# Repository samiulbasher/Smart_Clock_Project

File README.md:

# Smart_Clock_Project
Smart ESP8266 based real time clock

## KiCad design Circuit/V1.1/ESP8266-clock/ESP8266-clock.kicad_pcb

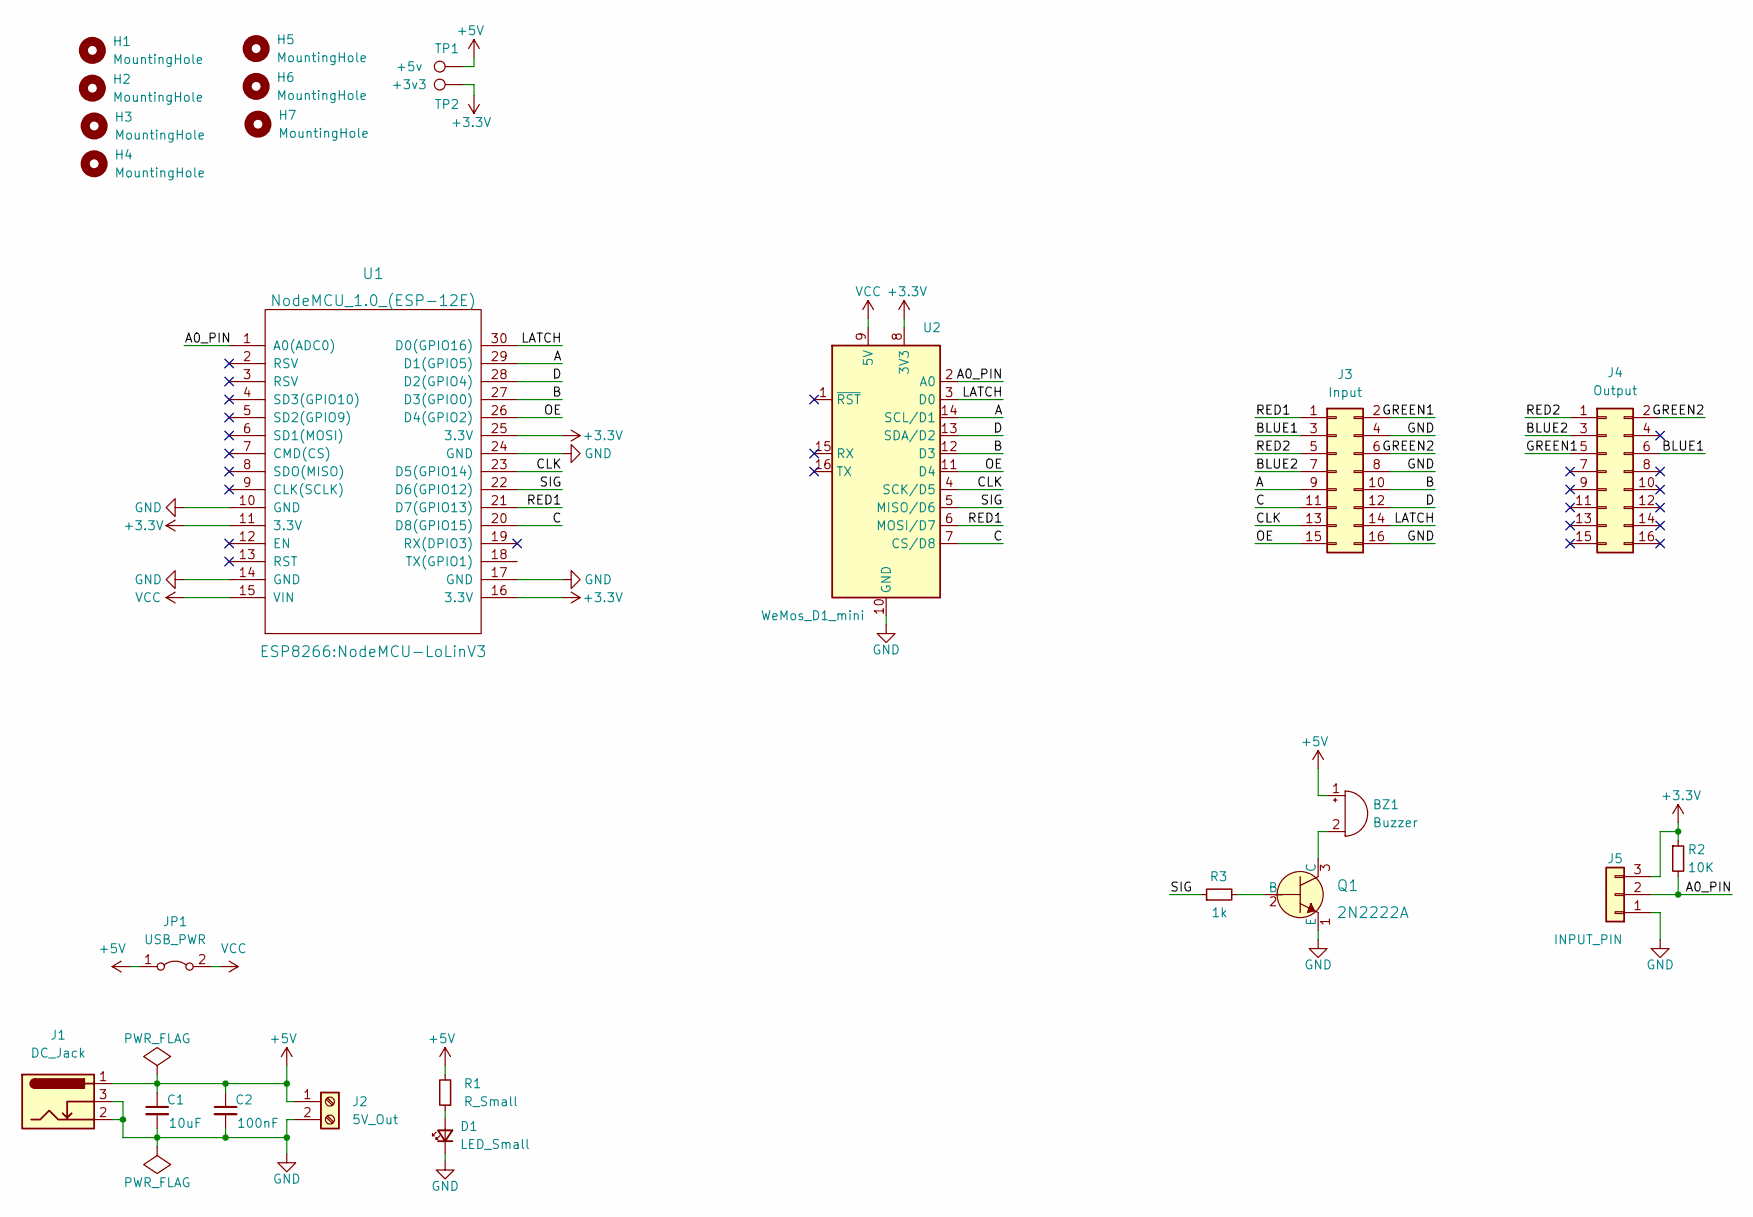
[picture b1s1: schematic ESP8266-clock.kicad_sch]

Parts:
BZ1: Buzzer; Buzzer_12x9.5RM7.6
C1: 10uF; CP_Radial_D5.0mm_P2.50mm
C2: 100nF; C_Disc_D3.0mm_W2.0mm_P2.50mm
D1: LED_Small; LED_D3.0mm
H1, H2, H3, H4: MountingHole; MountingHole_2.5mm
H5, H6, H7: MountingHole; MountingHole_3.5mm_Pad_Via
J1: DC_Jack; BarrelJack_Horizontal
J2: 5V_Out; TerminalBlock_Phoenix_PT-1,5-2-5.0-H_1x02_P5.00mm_Horizontal
J3: Input; PinHeader_2x08_P2.54mm_Vertical
J4: Output; PinHeader_2x08_P2.54mm_Vertical
J5: INPUT_PIN; Molex_KK-254_AE-6410-03A_1x03_P2.54mm_Vertical
JP1: USB_PWR; PinHeader_1x02_P2.54mm_Vertical
Q1: 2N2222A; TO-92-3_Formed_Leads; MPN 2N2222A; Digi-Key_PN 2N2222ACS-ND
R1: R_Small; R_Axial_DIN0204_L3.6mm_D1.6mm_P2.54mm_Vertical
R2: 10K; R_Axial_DIN0204_L3.6mm_D1.6mm_P7.62mm_Horizontal
R3: 1k; R_Axial_DIN0204_L3.6mm_D1.6mm_P2.54mm_Vertical
TP1: +5v; TestPoint_Pad_D1.0mm
TP2: +3v3; TestPoint_Pad_D1.0mm
U1: NodeMCU_1.0_(ESP-12E); NodeMCU-LoLinV3
U2: WeMos_D1_mini; WEMOS_D1_mini_light

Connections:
+3V3: J5.3, R2.1, TP2.1, U1.11 (3.3V), U1.16 (3.3V), U1.25 (3.3V), U2.8 (3V3)
+5V: BZ1.1 (-), C1.1, C2.1, J1.1, J2.1, JP1.1 (A), R1.2, TP1.1
/A: J3.9, U1.29 (D1(GPIO5)), U2.14 (SCL/D1)
/A0_PIN: J5.2, R2.2, U1.1 (A0(ADC0)), U2.2 (A0)
/B: J3.10, U1.27 (D3(GPIO0)), U2.12 (D3)
/BLUE1: J3.3, J4.6
/BLUE2: J3.7, J4.3
/C: J3.11, U1.20 (D8(GPIO15)), U2.7 (CS/D8)
/CLK: J3.13, U1.23 (D5(GPIO14)), U2.4 (SCK/D5)
/D: J3.12, U1.28 (D2(GPIO4)), U2.13 (SDA/D2)
/GREEN1: J3.2, J4.5
/GREEN2: J3.6, J4.2
/LATCH: J3.14, U1.30 (D0(GPIO16)), U2.3 (D0)
/OE: J3.15, U1.26 (D4(GPIO2)), U2.11 (D4)
/RED1: J3.1, U1.21 (D7(GPIO13)), U2.6 (MOSI/D7)
/RED2: J3.5, J4.1
/SIG: R3.1, U1.22 (D6(GPIO12)), U2.5 (MISO/D6)
GND: C1.2, C2.2, D1.1 (K), J1.2, J1.3, J2.2, J3.4, J3.8, J3.16, J5.1, Q1.1 (E), U1.10 (GND), U1.14 (GND), U1.17 (GND), U1.24 (GND), U2.10 (GND)
unnamed: BZ1.2 (+), Q1.3 (C)
unnamed: D1.2 (A), R1.1
unnamed: Q1.2 (B), R3.2
VCC: JP1.2 (B), U1.15 (VIN), U2.9 (5V)

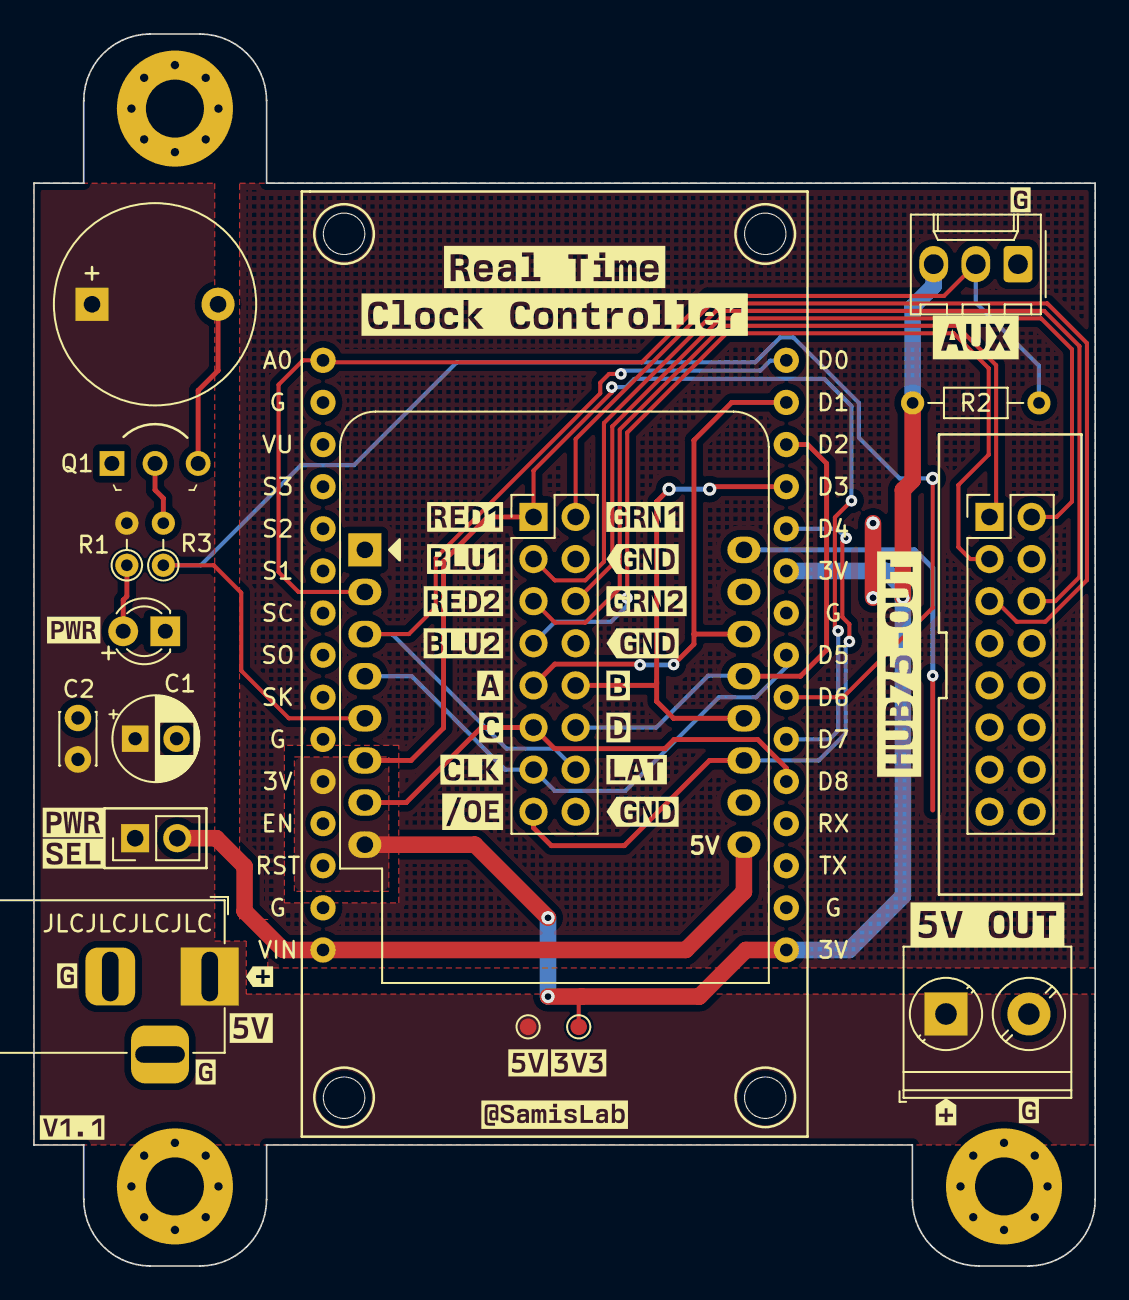
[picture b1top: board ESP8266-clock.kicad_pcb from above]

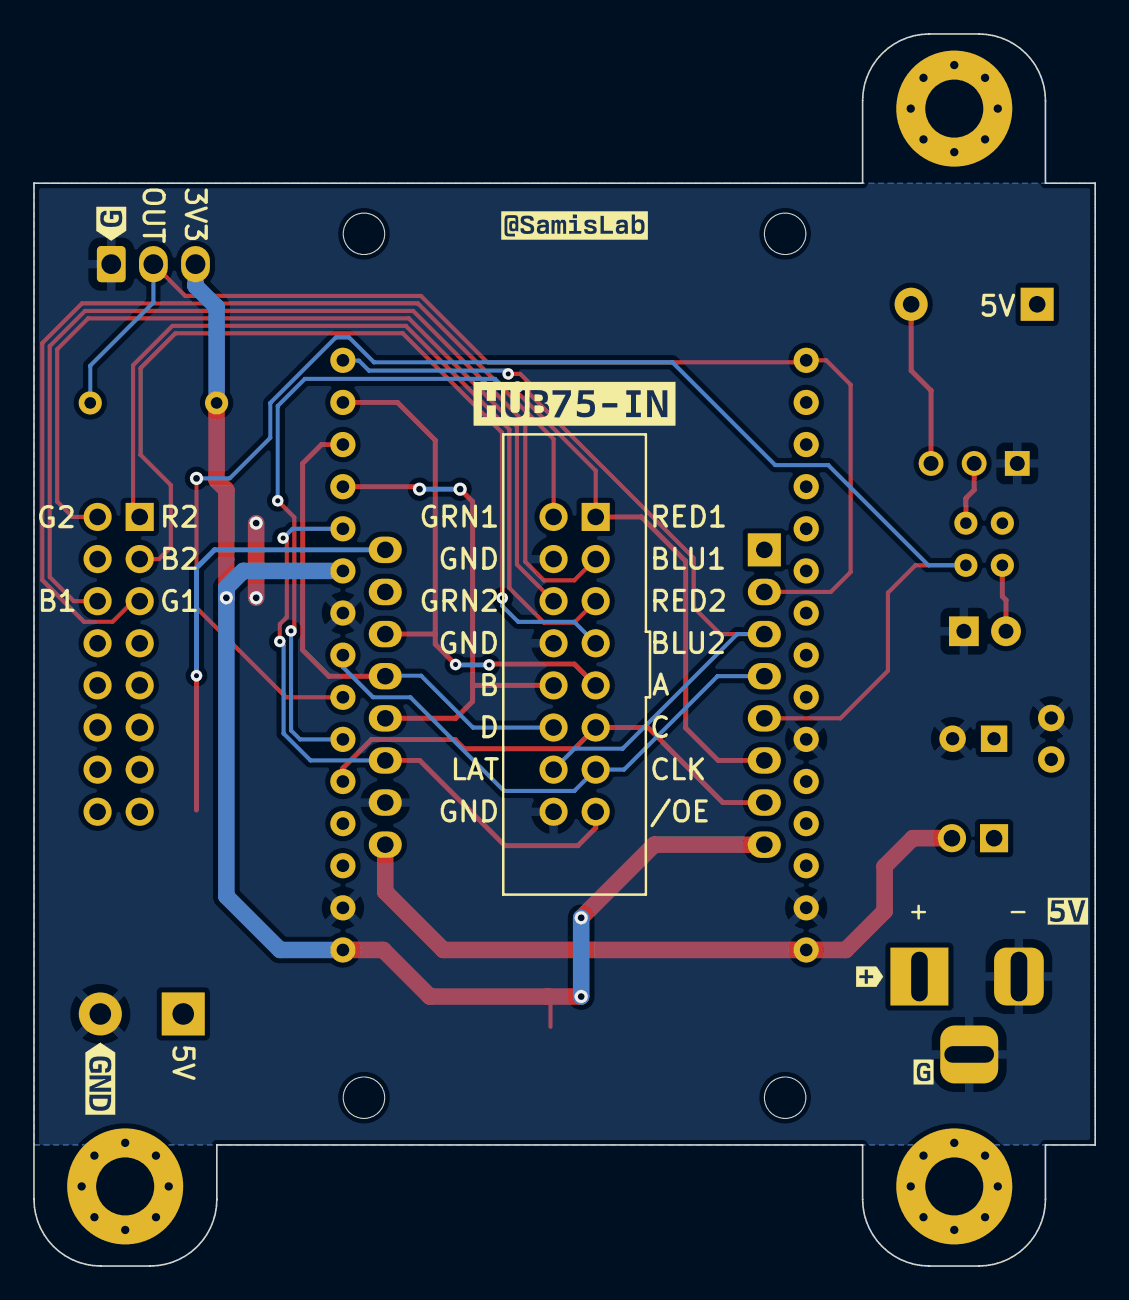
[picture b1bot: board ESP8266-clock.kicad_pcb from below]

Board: 2 copper layers, 64.0 x 74.3 mm, 67 parts (7 on the bottom side), 22 nets.

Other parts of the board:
kibuzzard-67C66AAA: G***; kibuzzard-67C66AAA
kibuzzard-67C66AFA: G***; kibuzzard-67C66AFA
kibuzzard-67C66B4C: G***; kibuzzard-67C66B4C
kibuzzard-67C66B15: G***; kibuzzard-67C66B15
kibuzzard-67C66B28: G***; kibuzzard-67C66B28
kibuzzard-67C66B36: G***; kibuzzard-67C66B36
kibuzzard-67C66B42: G***; kibuzzard-67C66B42
kibuzzard-67C66B74: G***; kibuzzard-67C66B74
kibuzzard-67C66F80: G***; kibuzzard-67C66F80
kibuzzard-67C66F98: G***; kibuzzard-67C66F98
kibuzzard-67C66FB5: G***; kibuzzard-67C66FB5
kibuzzard-67C66FBF: G***; kibuzzard-67C66FBF
kibuzzard-67C66FC9: G***; kibuzzard-67C66FC9
kibuzzard-67C66FDB, kibuzzard-67C66FDB#2, kibuzzard-67C66FDB#3: G***; kibuzzard-67C66FDB
kibuzzard-67C67BA5: G***; kibuzzard-67C67BA5
kibuzzard-67C67BB4: G***; kibuzzard-67C67BB4
kibuzzard-67C642C7: G***; kibuzzard-67C642C7
kibuzzard-67C643A6: G***; kibuzzard-67C643A6
kibuzzard-67C644C4: G***; kibuzzard-67C644C4
kibuzzard-67C648F1: G***; kibuzzard-67C648F1
kibuzzard-67C664FA: G***; kibuzzard-67C664FA
kibuzzard-67C684FA: G***; kibuzzard-67C684FA
kibuzzard-67C685CE: G***; kibuzzard-67C685CE
kibuzzard-67C6473C: G***; kibuzzard-67C6473C
kibuzzard-67C6875C: G***; kibuzzard-67C6875C
kibuzzard-67C64864: G***; kibuzzard-67C64864
kibuzzard-67C67064: G***; kibuzzard-67C67064
kibuzzard-67C67223: G***; kibuzzard-67C67223
kibuzzard-67C67309, kibuzzard-67C67309#2: G***; kibuzzard-67C67309
kibuzzard-651A1A52: G***; kibuzzard-651A1A52
kibuzzard-6514EA0E, kibuzzard-6514EA0E#2, kibuzzard-6514EA0E#3: G***; kibuzzard-6514EA0E
kibuzzard-6514EFEE, kibuzzard-6514EFEE#2, kibuzzard-6514EFEE#3, kibuzzard-6514EFEE#4: G***; kibuzzard-6514EFEE
kibuzzard-6997A622: G***; kibuzzard-6997A622
kibuzzard-69475C67: G***; kibuzzard-69475C67

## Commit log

2026-02-20 initial upload
2026-02-20 remove_unwanted_code
